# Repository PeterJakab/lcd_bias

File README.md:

lcd_bias
========

LCD bias voltage generator circuit for using 5V character LCDs on 3 volts

Please visit the project page at http://jap.hu/electronic/lcd_at_3_volts.html

This is the eagle v6 schematic and board layout for the charge pump circuit.
You can buy the assembled and tested board in my Tindie store
at https://www.tindie.com/stores/jap/

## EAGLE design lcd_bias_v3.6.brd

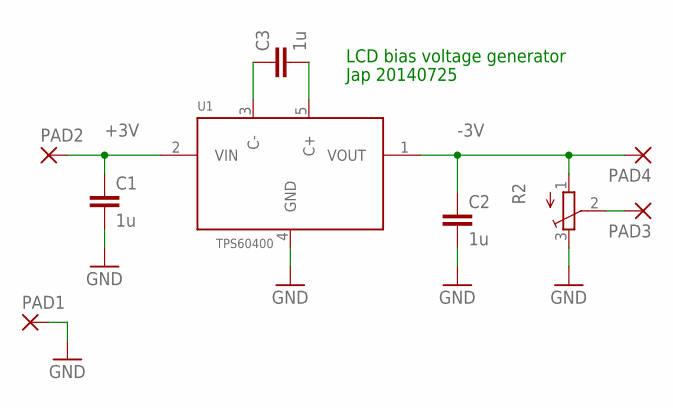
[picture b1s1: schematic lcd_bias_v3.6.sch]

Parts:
C1, C2, C3: 1u; C0603K
PAD1, PAD2, PAD3, PAD4: 1,6/0,8
R2: TRIMMER3305; RTRIM3305
U1: TPS60400; SOT23-5

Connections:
+3V: C1.1, PAD2.1, U1.2 (VIN)
-3V: C2.1, PAD4.1, R2.1 (A), U1.1 (VOUT)
GND: C1.2, C2.2, PAD1.1, R2.3 (E), U1.4 (GND)
unnamed: PAD3.1, R2.2 (S)
unnamed: C3.1, U1.3 (C-)
unnamed: C3.2, U1.5 (C+)

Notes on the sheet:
LCD bias voltage generator
Jap 20140725

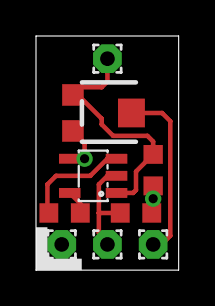
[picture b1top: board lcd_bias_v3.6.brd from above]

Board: 2 copper layers, 7.9 x 13.0 mm, 9 parts (0 on the bottom side), 6 nets.

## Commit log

2014-09-28 modified: README.md new file: lcd_bias_v3.6.brd new file: lcd_bias_v3.6.sch new file: lcd_bias_v3.6.sch.png
